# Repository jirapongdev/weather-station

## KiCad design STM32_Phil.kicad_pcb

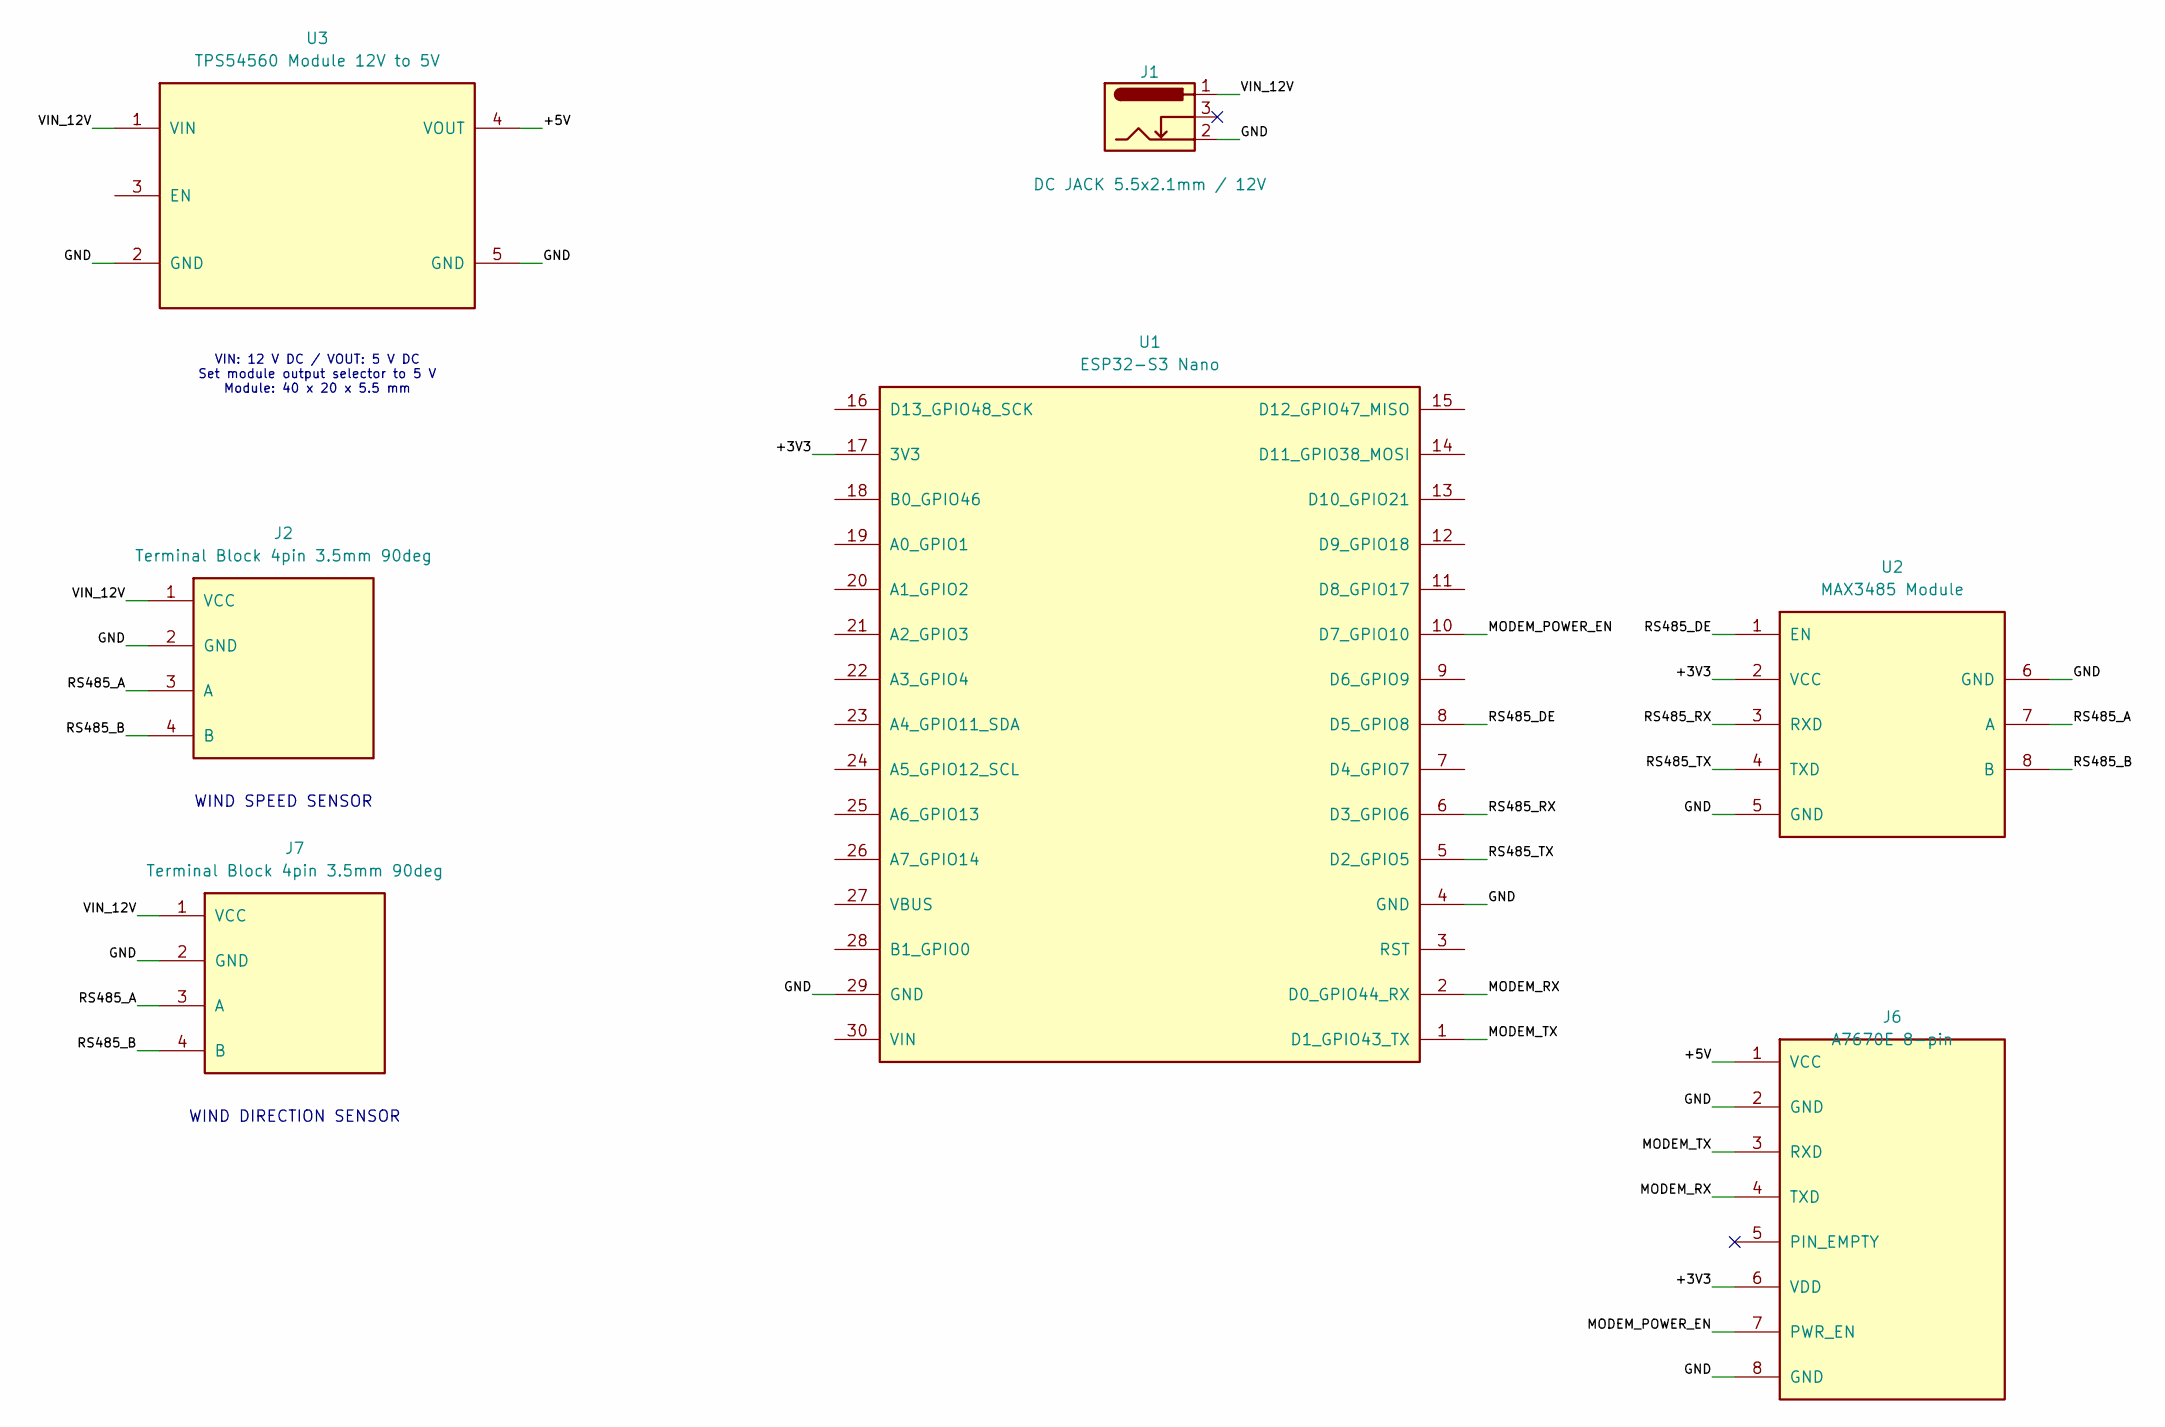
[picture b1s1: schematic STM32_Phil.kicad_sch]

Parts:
J1: DC JACK 5.5x2.1mm / 12V; DCJack_5.5x2.1_Horizontal_REFERENCE
J2, J7: Terminal Block 4pin 3.5mm 90deg; TerminalBlock_PlugHeader_1x04_P3.50_Horizontal_REFERENCE
J6: A7670E 8-pin; XH_Style_1x08_P2.54_REFERENCE
U1: ESP32-S3 Nano; ESP32_S3_Nano_30Pin_Image
U2: MAX3485 Module; MAX3485_Module_5plus3_Image_REFERENCE
U3: TPS54560 Module 12V to 5V; TPS54560_Module_40x20_D1.00_REFERENCE

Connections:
/+3V3: J6.6 (VDD), U1.17 (3V3), U2.2 (VCC)
/+5V: J6.1 (VCC), U3.4 (VOUT)
/GND: J1.2, J2.2 (GND), J6.2 (GND), J6.8 (GND), J7.2 (GND), U1.4 (GND), U1.29 (GND), U2.5 (GND), U2.6 (GND), U3.2 (GND), U3.5 (GND)
/MODEM_POWER_EN: J6.7 (PWR_EN), U1.10 (D7_GPIO10)
/MODEM_RX: J6.4 (TXD), U1.2 (D0_GPIO44_RX)
/MODEM_TX: J6.3 (RXD), U1.1 (D1_GPIO43_TX)
/RS485_A: J2.3 (A), J7.3 (A), U2.7 (A)
/RS485_B: J2.4 (B), J7.4 (B), U2.8 (B)
/RS485_DE: U1.8 (D5_GPIO8), U2.1 (EN)
/RS485_RX: U1.6 (D3_GPIO6), U2.3 (RXD)
/RS485_TX: U1.5 (D2_GPIO5), U2.4 (TXD)
/VIN_12V: J1.1, J2.1 (VCC), J7.1 (VCC), U3.1 (VIN)

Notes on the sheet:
WIND SPEED SENSOR
WIND DIRECTION SENSOR
VIN: 12 V DC / VOUT: 5 V DC Set module output selector to 5 V Module: 40 x 20 x 5.5 mm

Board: 2 copper layers, 8 parts (0 on the bottom side), 12 nets, no tracks yet.

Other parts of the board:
M1: A7670E 53x32 M2 REFERENCE; A7670E_Module_53x32_M2_Mounting_REFERENCE
